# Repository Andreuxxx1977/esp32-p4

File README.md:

KiCad 10 renders of hardware/output/esp32p4_extreme.kicad_pcb (commit ff21bf26fdb5f9f9c406fee58010d21b526a7d88), published by CI.

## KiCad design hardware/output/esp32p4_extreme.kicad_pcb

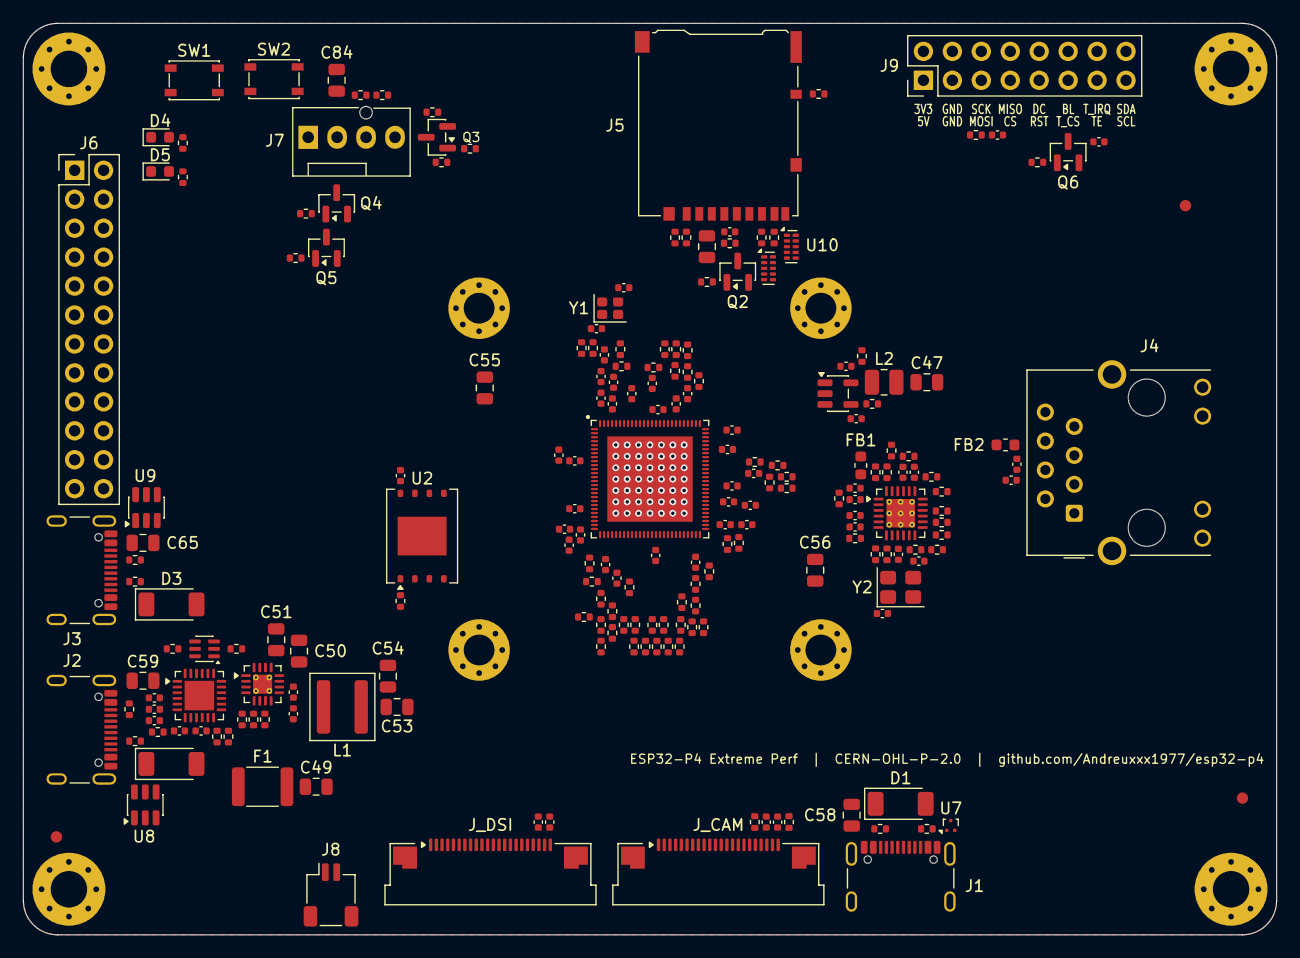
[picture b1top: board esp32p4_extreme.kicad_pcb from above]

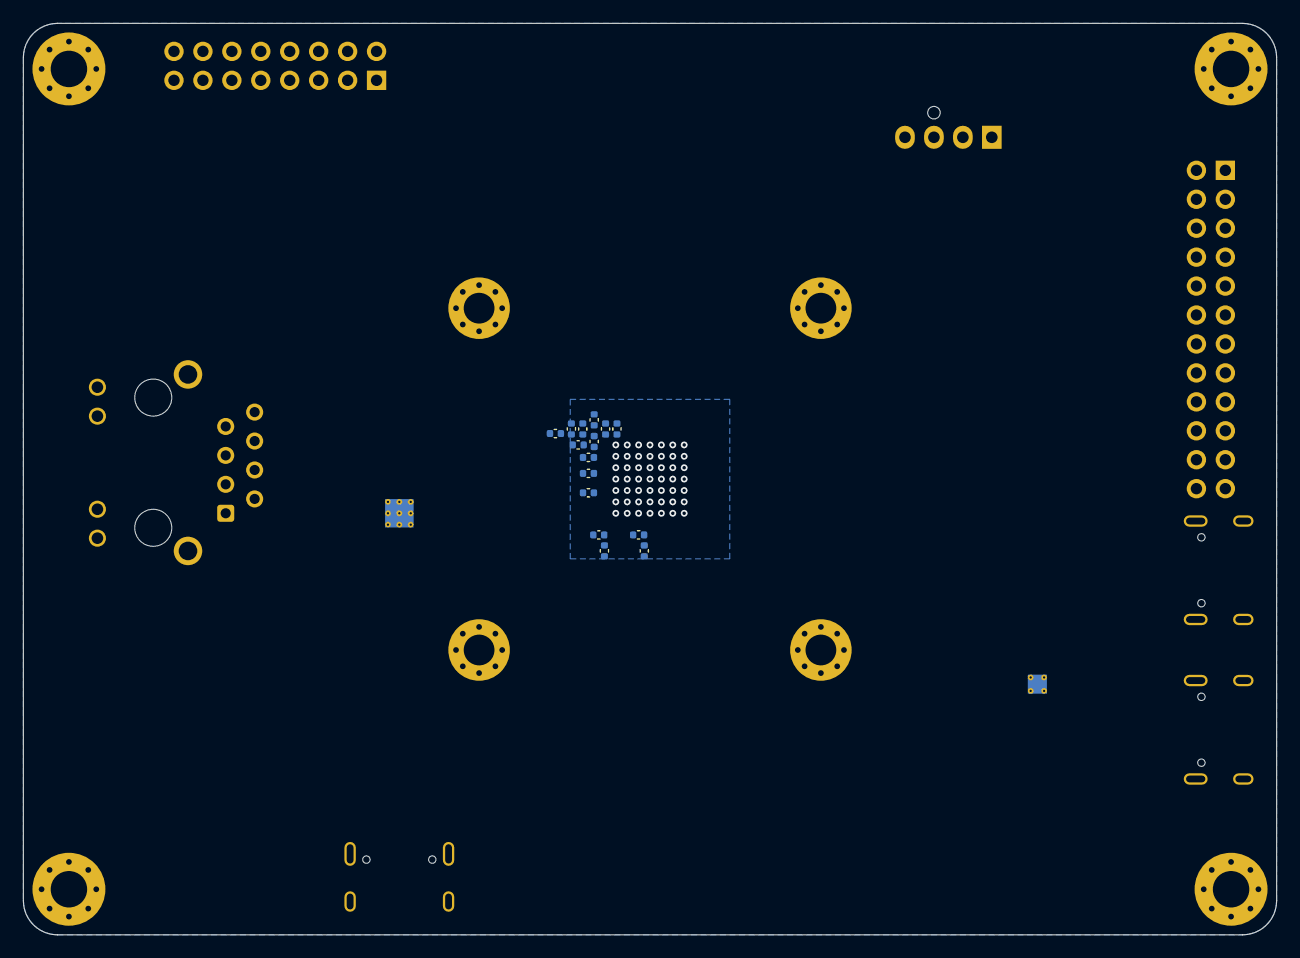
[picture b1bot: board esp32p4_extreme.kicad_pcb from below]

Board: 4 copper layers, 110.0 x 80.0 mm, 234 parts (15 on the bottom side), 175 nets, no tracks yet.

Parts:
C1, C3, C4, C7, C10, C13, C15, C17, C19, C21, C27, C29, C32, C34, C35, C37, C39, C40, C45, C52, C60, C62, C64, C70, C71, C72, C75, C79, C81, C83, C86: 100nF; C_0402_1005Metric
C2, C6, C28, C31, C33, C41: 10uF; C_0402_1005Metric
C5, C8, C11, C16, C18, C20, C22, C23, C24, C25, C26, C30, C36, C42, C61, C63, C68, C69, C73, C80, C82: 1uF; C_0402_1005Metric
C9, C12, C38, C76: 10nF; C_0402_1005Metric
C14, C46: 4.7uF; C_0402_1005Metric
C43, C44: 12pF; C_0402_1005Metric
C47, C53, C54: 22uF; C_0805_2012Metric
C48: 22pF; C_0402_1005Metric
C49, C50, C51, C58, C59, C65, C78, C84: 10uF; C_0805_2012Metric
C55, C56: 47uF; C_0805_2012Metric
C57: 3.3nF; C_0402_1005Metric
C66, C67: 18pF; C_0402_1005Metric
C74: 470pF; C_0402_1005Metric
C77, C85: 10pF; C_0402_1005Metric
D1, D2, D3: PMEG4050EP; D_SOD-128
D4: Green; LED_0603_1608Metric
D5: Red; LED_0603_1608Metric
F1: PTC 2.5A; Fuse_1812_4532Metric
FB1, FB2: 220R@100MHz; L_0603_1608Metric
FID1, FID2, FID3: Fiducial; Fiducial_1mm_Mask2mm
H1, H2, H3, H4: M2.5; MountingHole_2.7mm_M2.5_Pad_Via
H5, H6, H7, H8: M3; MountingHole_3.2mm_M3_Pad_Via
J1, J2, J3: USB-C; USB_C_Receptacle_GCT_USB4105-xx-A_16P_TopMnt_Horizontal
J4: RJ45 MagJack; RJ45_Hanrun_HR911105A_Horizontal
J5: microSD; microSD_HC_Hirose_DM3AT-SF-PEJM5
J6: 2x12 header; PinHeader_2x12_P2.54mm_Vertical
J7: Fan 4P; FanPinHeader_1x04_P2.54mm_Vertical
J8: JST-SH 2P; JST_SH_SM02B-SRSS-TB_1x02-1MP_P1.00mm_Horizontal
J9: 2x8 header; PinHeader_2x08_P2.54mm_Vertical
J_CAM: FPC 22P 0.5mm; Amphenol_F32Q-1A7x1-11022_1x22-1MP_P0.5mm_Horizontal
J_DSI: FPC 22P 0.5mm; Amphenol_F32Q-1A7x1-11022_1x22-1MP_P0.5mm_Horizontal
L1: 2.2uH; L_Coilcraft_XAL5030-XXX
L2: 2.2uH; L_1008_2520Metric
Q1: MMDT3904; SOT-363_SC-70-6
Q2, Q4, Q6: AO3401A; SOT-23
Q3, Q5: AO3400A; SOT-23
R1, R2, R3, R11, R12, R13, R14, R15, R16, R17, R18, R28, R29, R59, R60, R61, R62, R63, R64, R72, R73, R74, R75, R76, R77, R78, R79, R80, R81, R82, R83: 0R; R_0402_1005Metric
R4, R5: 4.02k; R_0402_1005Metric
R6, R7, R8, R19, R35, R36, R49, R50, R51, R70, R71, R88, R90, R91: 10k; R_0402_1005Metric
R9, R25, R34, R92, R93: 1k; R_0402_1005Metric
R10: 1M; R_0402_1005Metric
R20, R21: 499k; R_0402_1005Metric
R22: 75k; R_0402_1005Metric
R23: 24k; R_0402_1005Metric
R24, R87, R89, R95: 100k; R_0402_1005Metric
R26, R27, R30, R31, R37, R38: 5.1k; R_0402_1005Metric
R32: 22.1k; R_0402_1005Metric
R33: 47.5k; R_0402_1005Metric
R39, R40, R41, R42, R43, R44, R45, R46, R94: 22; R_0402_1005Metric
R47: 33; R_0402_1005Metric
R48: 12.1k; R_0402_1005Metric
R52: 1.5k; R_0402_1005Metric
R53, R54, R55, R56: 49.9; R_0402_1005Metric
R57, R58: 330; R_0402_1005Metric
R65, R66, R67, R68, R69: 51k; R_0402_1005Metric
R84, R85: 2.2k; R_0402_1005Metric
R86: 100; R_0402_1005Metric
SW1, SW2: Tactile; SW_SPST_PTS810
U1: ESP32-P4NRW32X; ESP32-P4
U2: W25Q256JV 32MB; WSON-8-1EP_8x6mm_P1.27mm_EP3.4x4.3mm
U3: TPS62130; VQFN-16-1EP_3x3mm_P0.5mm_EP1.68x1.68mm_ThermalVias
U4: TLV62569; SOT-23-5
U5: LAN8720A; VQFN-24-1EP_4x4mm_P0.5mm_EP2.5x2.5mm_ThermalVias
U6: CP2102N; QFN-24-1EP_4x4mm_P0.5mm_EP2.6x2.6mm
U7: TPD2EUSB30; Texas_DRT-3
U8, U9: USBLC6-2SC6; SOT-23-6
U10, U11: TPD4E05U06; USON-10_2.5x1.0mm_P0.5mm
Y1: 40MHz 10ppm; Crystal_SMD_2016-4Pin_2.0x1.6mm
Y2: 25MHz; Crystal_SMD_3225-4Pin_3.2x2.5mm

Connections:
+3V3: C1.1, C2.1, C3.1, C19.1, C20.1, C27.1, C28.1, C32.1, C33.1, C37.1, C38.1, C39.1, C46.1, C53.1, C54.1, C55.1, C56.1, C60.1, C61.1, C62.1, C63.1, C64.1, C72.1, C80.1, C81.1, C82.1, C83.1, FB1.1, J6.1, J9.1, J_CAM.22, J_DSI.22, L1.2, Q2.2, Q6.2, R1.1, R2.1, R6.1, R7.1, R8.1, R22.1, R24.1, R25.1, R34.1, R51.1, R52.1, R71.1, R84.1, R85.1, R90.1, R91.1, U1.9, U1.21, U1.62, U1.75, U1.77, U1.96, U1.101, U3.14, U4.4, U5.9, U6.5, U6.6, U6.7
BOOT_BTN: Q1.3, R9.2, SW2.1
BUCK_FB: R22.2, R23.1, U3.5
BUCK_PG: R24.2, U3.4
BUCK_SS: C57.1, U3.9
BUCK_SW: L1.1, U3.1, U3.2, U3.3
CAM_CLK_N: J_CAM.8, R77.2
CAM_CLK_P: J_CAM.9, R76.2
CAM_D0_N: J_CAM.2, R73.2
CAM_D0_P: J_CAM.3, R72.2
CAM_D1_N: J_CAM.5, R75.2
CAM_D1_P: J_CAM.6, R74.2
CAM_EN: J_CAM.17, U1.13
CAM_IO1: J_CAM.18, U1.14
CHIP_PU: C42.1, Q1.6, R6.2, SW1.1, U1.103
CP_DTR: Q1.4, R35.1, U6.23
CP_RST_N: R34.2, U6.9
CP_RTS: Q1.1, R36.1, U6.19
CP_VBUS_SENSE: R32.2, R33.1, U6.8
CSI_CLK_N: R77.1, U1.45
CSI_CLK_P: R76.1, U1.44
CSI_D0_N: R73.1, U1.42
CSI_D0_P: R72.1, U1.43
CSI_D1_N: R75.1, U1.46
CSI_D1_P: R74.1, U1.47
CSI_REXT: R5.1, U1.48
DISP_CLK_N: J_DSI.8, R83.2
DISP_CLK_P: J_DSI.9, R82.2
DISP_D0_N: J_DSI.2, R79.2
DISP_D0_P: J_DSI.3, R78.2
DISP_D1_N: J_DSI.5, R81.2
DISP_D1_P: J_DSI.6, R80.2
DSI_CLK_N: R83.1, U1.37
DSI_CLK_P: R82.1, U1.38
DSI_D0_N: R79.1, U1.40
DSI_D0_P: R78.1, U1.39
DSI_D1_N: R81.1, U1.36
DSI_D1_P: R80.1, U1.35
DSI_REXT: R4.1, U1.34
ETH_CT: C75.1, C76.1, FB2.2, J4.4, J4.5
ETH_LED_LINK_A: J4.9, R57.2
ETH_LED_SPEED_A: J4.12, R58.2
ETH_MDC: U1.61, U5.13
ETH_MDIO: R52.2, U1.95, U5.12
ETH_PHY_RST_N: R51.2, U1.94, U5.15
ETH_RX_N: J4.6, R56.1, U5.22
ETH_RX_P: J4.3, R55.1, U5.23
ETH_TX_N: J4.2, R54.1, U5.20
ETH_TX_P: J4.1, R53.1, U5.21
FAN_5V: C84.1, J7.2, Q4.3, R88.2
FAN_EN: Q5.1, R90.2, U1.12
FAN_HS_G: Q4.1, Q5.3, R89.2
FAN_PWM: R86.1, U1.10
FAN_PWM_G: Q3.1, R86.2, R87.1
FAN_PWM_OD: J7.4, Q3.3, R88.1
FAN_TACH: R92.2, U1.11
FAN_TACH_RAW: J7.3, R91.2, R92.1
FLASH_CK: R17.1, U1.32
FLASH_CK_M: R17.2, U2.6
FLASH_CS: R13.1, U1.27
FLASH_CS_M: R13.2, R19.2, U2.1
FLASH_D: R18.1, U1.33
FLASH_D_M: R18.2, U2.5
FLASH_HOLD: R16.1, U1.31
FLASH_HOLD_M: R16.2, U2.7
FLASH_Q: R14.1, U1.28
FLASH_Q_M: R14.2, U2.2
FLASH_WP: R15.1, U1.29
FLASH_WP_M: R15.2, U2.3
GND: C1.2, C2.2, C3.2, C4.2, C5.2, C6.2, C7.2, C8.2, C9.2, C10.2, C11.2, C12.2, C13.2, C14.2, C15.2, C16.2, C17.2, C18.2, C19.2, C20.2, C21.2, C22.2, C23.2, C24.2, C25.2, C26.2, C27.2, C28.2, C29.2, C30.2, C31.2, C32.2, C33.2, C34.2, C35.2, C36.2, C37.2, C38.2, C39.2, C40.2, C41.2, C42.2, C43.2, C44.2, C45.2, C46.2, C47.2, C49.2, C50.2, C51.2, C52.2, C53.2, C54.2, C55.2, C56.2, C57.2, C58.2, C59.2, C60.2, C61.2, C62.2, C63.2, C64.2, C65.2, C66.2, C67.2, C68.2, C69.2, C70.2, C71.2, C72.2, C73.2, C74.2, C75.2, C76.2, C77.2, C78.2, C79.2, C80.2, C81.2, C82.2, C83.2, C84.2, C85.2, C86.2, D4.1, D5.1, H1.1, H2.1, H3.1, H4.1, H5.1, H6.1, H7.1, H8.1, J1.A1, J1.A12, J1.B1, J1.B12, J1.SH, J2.A1, J2.A12, J2.B1, J2.B12, J2.SH, J3.A1, J3.A12, J3.B1, J3.B12, J3.SH, J4.8, J4.10, J4.11, J4.SH, J5.6, J5.9, J5.SH, J6.9, J6.10, J7.1, J8.2, J8.MP, J9.3, J9.4, J_CAM.1, J_CAM.4, J_CAM.7, J_CAM.10, J_CAM.13, J_CAM.16, J_CAM.19, J_CAM.MP, J_DSI.1, J_DSI.4, J_DSI.7, J_DSI.10, J_DSI.13, J_DSI.16, J_DSI.19, J_DSI.MP, Q3.2, Q5.2, R4.2, R5.2, R10.2, R21.2, R23.2, R26.2, R27.2, R30.2, R31.2, R33.2, R37.2, R38.2, R48.2, R49.2, R50.2, R70.2, R87.2, R95.2, SW1.2, SW2.2, U1.105, U2.4, U2.9, U3.6, U3.7, U3.8, U3.15, U3.16, U3.17, U4.2, U5.25, U6.2, U6.25, U7.3, U8.2, U9.2, U10.3, U10.8, U11.3, U11.8, Y1.2, Y1.4, Y2.2, Y2.4
GPIO0: J6.3, U1.104
GPIO1: J6.4, U1.1
GPIO2: J6.5, U1.2
GPIO3: J6.6, U1.3
GPIO4: J6.7, U1.4
GPIO5: J6.8, U1.5
GPIO16: J6.15, J9.12, U1.17
GPIO17: J6.16, J9.13, U1.18
GPIO18: J6.17, Q6.1, R95.1, U1.19
GPIO19: J6.18, J9.14, U1.20
GPIO22: J6.19, J9.7, U1.24
GPIO23: J6.20, J9.8, U1.25
GPIO32: J6.21, R94.1, U1.63
GPIO33: J6.22, J9.6, U1.64
GPIO53: J6.23, J9.9, U1.97
GPIO54: J6.24, J9.10, U1.98
HP_SW: L2.1, U4.3
I2C_SCL: J6.12, J9.16, J_CAM.20, J_DSI.20, R85.2, U1.8
I2C_SDA: J6.11, J9.15, J_CAM.21, J_DSI.21, R84.2, U1.7
J1_CC1: J1.A5, R26.1
J1_CC2: J1.B5, R27.1
J2_CC1: J2.A5, R30.1
J2_CC2: J2.B5, R31.1
J3_CC1: J3.A5, R37.1
J3_CC2: J3.B5, R38.1
LCD_BL_PWM: J_DSI.18, U1.55
LCD_RST: J_DSI.17, U1.56
LCD_SPI_BL: C86.1, J9.11, Q6.3
LCD_SPI_SCK: C85.1, J9.5, R94.2
LED_PWR_A: D4.2, R25.2
LED_STATUS: R93.1, U1.6
LED_STATUS_A: D5.2, R93.2
LP_UART_RXD: J6.14, U1.16
LP_UART_TXD: J6.13, U1.15
PHY_AVDD: C68.1, C69.1, C70.1, C71.1, FB1.2, FB2.1, R53.2, R54.2, R55.2, R56.2, U5.1, U5.19
PHY_LED1: R57.1, U5.3
PHY_LED2: R49.1, R58.1, U5.2
PHY_RBIAS: R48.1, U5.24
PHY_RXER: R50.1, U5.10
PHY_VDDCR: C73.1, C74.1, U5.6
PHY_XI: C66.1, U5.5, Y2.1
PHY_XO: C67.1, U5.4, Y2.3
Q1_B1: Q1.2, R35.2
Q1_B2: Q1.5, R36.2
RMII_CRS_DV: R46.2, U1.57
RMII_CRS_DV_PHY: R46.1, U5.11
RMII_REF_CLK: R47.2, U1.93
RMII_REF_CLK_PHY: R47.1, U5.14
RMII_RXD0: R44.2, U1.58
RMII_RXD0_PHY: R44.1, U5.8
RMII_RXD1: R45.2, U1.60
RMII_RXD1_PHY: R45.1, U5.7
RMII_TXD0: R41.1, U1.65
RMII_TXD0_PHY: R41.2, U5.17
RMII_TXD1: R7.2, R9.1, R42.1, U1.66
RMII_TXD1_PHY: R42.2, U5.18
RMII_TX_EN: R43.1, U1.92
RMII_TX_EN_PHY: R43.2, U5.16
SD_CLK: R63.1, U1.84
SD_CLK_C: C77.1, J5.5, R63.2, U11.1, U11.10
SD_CMD: R64.1, U1.86
SD_CMD_C: J5.3, R64.2, R69.1, U11.2, U11.9
SD_D0: R59.1, U1.80
SD_D0_C: J5.7, R59.2, R65.1, U10.1, U10.10
SD_D1: R60.1, U1.81
SD_D1_C: J5.8, R60.2, R66.1, U10.2, U10.9
SD_D2: R61.1, U1.82
SD_D2_C: J5.1, R61.2, R67.1, U10.4, U10.7
SD_D3: R62.1, U1.83
SD_D3_C: J5.2, R62.2, R68.1, U10.5, U10.6
SD_DET: J5.10, R71.2, U1.23, U11.4, U11.7
SD_PWR_EN: Q2.1, R70.1, U1.22
SD_VDD: C78.1, C79.1, J5.4, Q2.3
STRAP_GPIO36: R8.2, U1.68
UART0_RXD: U1.70, U6.21
UART0_TXD: U1.69, U6.20
USB1_D_N: J1.A7, J1.B7, R29.1, U7.2
USB1_D_P: J1.A6, J1.B6, R28.1, U7.1
USB2_D_N: J2.A7, J2.B7, U6.4, U8.3, U8.4
USB2_D_P: J2.A6, J2.B6, U6.3, U8.1, U8.6
USB3_D_N: J3.A7, J3.B7, R40.1, U9.3, U9.4
USB3_D_P: J3.A6, J3.B6, R39.1, U9.1, U9.6
USBHS_D_N: R29.2, U1.49
USBHS_D_P: R10.1, R28.2, U1.50
USJ_D_N: R40.2, U1.52
USJ_D_P: R39.2, U1.53
VBUS1: C58.1, D1.2, J1.A4, J1.A9, J1.B4, J1.B9
VBUS2: C59.1, D2.2, J2.A4, J2.A9, J2.B4, J2.B9, R32.1, U8.5
VBUS3: C65.1, D3.2, J3.A4, J3.A9, J3.B4, J3.B9, U9.5
VDDO_4_SDIO: C26.1, C34.1, R65.2, R66.2, R67.2, R68.2, R69.2, U1.74, U1.85
VDDO_FLASH: C7.1, C8.1, C23.1, C45.1, R19.1, U1.30, U1.71, U2.8
VDDO_PSRAM: C17.1, C18.1, C21.1, C22.1, C24.1, U1.59, U1.67, U1.72
VDD_BAT: C40.1, C41.1, R2.2, U1.102
VDD_HP: C4.1, C5.1, C6.1, C29.1, C30.1, C31.1, C35.1, C36.1, C47.1, C48.1, L2.2, R3.1, R20.1, U1.26, U1.76, U1.91
VDD_HP1_PAD: C15.1, C16.1, R3.2, U1.54
VDD_HP_EN: U1.79, U4.1
VDD_HP_FB: C48.2, R20.2, R21.1, U1.78, U4.5
VDD_MIPI_PHY: C9.1, C10.1, C11.1, C25.1, U1.41, U1.73
VDD_USBPHY: C12.1, C13.1, C14.1, R1.2, U1.51
VSYS_5V: C49.1, C50.1, C51.1, C52.1, F1.2, J6.2, J8.1, J9.2, Q4.2, R89.1, U3.10, U3.11, U3.12, U3.13
VSYS_OR: D1.1, D2.1, D3.1, F1.1
XTAL_N: R12.1, U1.99
XTAL_N_Y: C44.1, R12.2, Y1.3
XTAL_P: R11.1, U1.100
XTAL_P_Y: C43.1, R11.2, Y1.1

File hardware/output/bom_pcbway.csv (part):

Item #,Designator,Quantity,Value/Name,Package/Footprint,Manufacturer Part Number (MPN),Manufacturer,Description,Mount (SMD/THT),LCSC #,Assembly note
1,"C1, C3, C4, C7, C10, C13, C15, C17, C19, C21, C27, C29, C32, C34, C35, C37, C39, C40, C45, C52, C60, C62, C64, C70, C71, C72, C75, C79, C81, C83, C86",31,100nF,0402 [C_0402_1005Metric],CL05B104KO5NNNC,Samsung Electro-Mechanics,MLCC 100nF 16V X7R,SMD,C1525,
2,"C2, C6, C28, C31, C33, C41",6,10uF,0402 [C_0402_1005Metric],CL05A106MQ5NUNC,Samsung Electro-Mechanics,MLCC 10uF 6.3V X5R,SMD,C15525,
3,"C5, C8, C11, C16, C18, C20, C22, C23, C24, C25, C26, C30, C36, C42, C61, C63, C68, C69, C73, C80, C82",21,1uF,0402 [C_0402_1005Metric],CL05A105KA5NQNC,Samsung Electro-Mechanics,MLCC 1uF 25V X5R,SMD,C52923,
4,"C9, C12, C38, C76",4,10nF,0402 [C_0402_1005Metric],CL05B103KB5NNNC,Samsung Electro-Mechanics,MLCC 10nF 50V X7R,SMD,C15195,
5,"C14, C46",2,4.7uF,0402 [C_0402_1005Metric],CL05A475MP5NRNC,Samsung Electro-Mechanics,MLCC 4.7uF 10V X5R,SMD,C23733,
6,"C43, C44",2,12pF,0402 [C_0402_1005Metric],CL05C120JB5NNNC,Samsung Electro-Mechanics,MLCC 12pF 50V C0G,SMD,,no LCSC number
7,"C47, C53, C54",3,22uF,0805 [C_0805_2012Metric],CL21A226MQQNNNE,Samsung Electro-Mechanics,MLCC 22uF 6.3V X5R,SMD,C5674,
8,C48,1,22pF,0402 [C_0402_1005Metric],CL05C220JB5NNNC,Samsung Electro-Mechanics,MLCC 22pF 50V C0G,SMD,C70464,
9,"C49, C50, C51, C58, C59, C65, C78, C84",8,10uF,0805 [C_0805_2012Metric],CL21A106KAYNNNE,Samsung Electro-Mechanics,MLCC 10uF 25V X5R,SMD,C15850,
10,"C55, C56",2,47uF,0805 [C_0805_2012Metric],CL21A476MQYNNNE,Samsung Electro-Mechanics,MLCC 47uF 6.3V X5R,SMD,C16780,
11,C57,1,3.3nF,0402 [C_0402_1005Metric],CL05B332KB5NNNC,Samsung Electro-Mechanics,MLCC 3.3nF 50V X7R,SMD,C26404,
12,"C66, C67",2,18pF,0402 [C_0402_1005Metric],CL05C180JB5NNNC,Samsung Electro-Mechanics,MLCC 18pF 50V C0G,SMD,C307443,
13,C74,1,470pF,0402 [C_0402_1005Metric],CL05B471KB5NNNC,Samsung Electro-Mechanics,MLCC 470pF 50V X7R,SMD,C26412,
14,"D1, D2, D3",3,PMEG4050EP,SOD-128 [D_SOD-128],"PMEG4050EP,115",Nexperia,40 V 5 A low-VF Schottky (~0.4 V @ 2.5 A) -- VBUS OR-ing,SMD,C96235,
15,D4,1,Green,0603 [LED_0603_1608Metric],150060GS75000,Wurth Elektronik,Green LED,SMD,C5252984,
16,D5,1,Red,0603 [LED_0603_1608Metric],150060RS75000,Wurth Elektronik,Red LED,SMD,C3030991,
17,F1,1,PTC 2.5A,1812 [Fuse_1812_4532Metric],MF-MSMF250/16X-2,Bourns,"Resettable fuse, 2.5 A hold / 5 A trip, 16 V, on VSYS",SMD,C210838,
18,"FB1, FB2",2,220R@100MHz,0603 [L_0603_1608Metric],BLM18PG221SN1D,Murata,"Ferrite bead 220 ohm, 1.4 A",SMD,C80165,
19,"J1, J2, J3",3,USB-C,"USB Type-C 16P, top-mount [USB_C_Receptacle_GCT_USB4105-xx-A_16P_TopMnt_Horizontal]",USB4105-GF-A,GCT,"USB 2.0 Type-C receptacle (UFP, 5.1k Rd); SMD contacts + 4 THT shell legs",SMD,C3020560,SMD with THT legs (paste-in-hole / hand-solder the legs)
20,J4,1,RJ45 MagJack,"RJ45 THT, integrated magnetics + 2 LEDs [RJ45_Hanrun_HR911105A_Horizontal]",HR911105A,HanRun,"RJ45 with 10/100 magnetics (1:1, CT) and green/yellow LEDs",THT,C12074,"THT, top side"
21,J5,1,microSD,"microSD push-push, SMT [microSD_HC_Hirose_DM3AT-SF-PEJM5]",DM3AT-SF-PEJM5,Hirose,microSD socket with card-detect switch,SMD,C114218,
22,J6,1,2x12 header,2x12 2.54 mm THT [PinHeader_2x12_P2.54mm_Vertical],61302421121,Wurth Elektronik,2x12 expansion header,THT,,"THT, top side; no LCSC number"
23,J7,1,Fan 4P,"2.54 mm 4-pin fan header, THT [FanPinHeader_1x04_P2.54mm_Vertical]",47053-1000,Molex,"Intel 4-wire PWM fan header (1 GND, 2 +V, 3 TACH, 4 PWM)",THT,C240840,"THT, top side"
24,J8,1,JST-SH 2P,"JST SH 1.0 mm 2P, SMT [JST_SH_SM02B-SRSS-TB_1x02-1MP_P1.00mm_Horizontal]",SM02B-SRSS-TB(LF)(SN),JST,Display backlight 5 V feed,SMD,C160402,
25,J9,1,2x8 header,2x8 2.54 mm THT [PinHeader_2x08_P2.54mm_Vertical],61301621121,Wurth Elektronik,2x8 SPI/I2C TFT display header (dupont-wire friendly),THT,,"THT, top side; no LCSC number"
26,"J_CAM, J_DSI",2,FPC 22P 0.5mm,"FPC 22P 0.5 mm, top contact, horizontal, SMT [Amphenol_F32Q-1A7x1-11022_1x22-1MP_P0.5mm_Horizontal]",F32Q-1A7H1-11022,Amphenol ICC,"22-pin 0.5 mm FPC, same top-contact part as Raspberry Pi 5 -> standard Pi cables, no mirroring",SMD,C3169253,
27,L1,1,2.2uH,5.3x5.5 mm shielded [L_Coilcraft_XAL5030-XXX],XAL5030-222MEC,Coilcraft,"2.2 uH, Isat 9.2 A, DCR 14.5 mOhm -- 3 A buck inductor",SMD,C920280,
28,L2,1,2.2uH,2520 (1008) metal alloy [L_1008_2520Metric],DFE252012F-2R2M=P2,Murata,"2.2 uH, Isat 3.3 A, 82 mOhm -- VDD_HP buck inductor",SMD,C576403,
29,Q1,1,MMDT3904,SOT-363 [SOT-363_SC-70-6],MMDT3904-7-F,Diodes Incorporated,Dual NPN for DTR/RTS auto-reset + boot-strap circuit,SMD,C83572,
30,"Q2, Q4, Q6",3,AO3401A,SOT-23 [SOT-23],AO3401A,Alpha & Omega Semiconductor,-30 V -4 A P-MOSFET (high-side load switch),SMD,C15127,
31,"Q3, Q5",2,AO3400A,SOT-23 [SOT-23],AO3400A,Alpha & Omega Semiconductor,30 V 5.7 A logic-level N-MOSFET (Vgs(th) 1.45 V max),SMD,C20917,
32,"R1, R2, R3, R11, R12, R13, R14, R15, R16, R17, R18, R28, R29, R59, R60, R61, R62, R63, R64, R72, R73, R74, R75, R76, R77, R78, R79, R80, R81, R82, R83",31,0R,0402 [R_0402_1005Metric],RC0402JR-070RL,YAGEO,"Thick-film resistor, jumper",SMD,C60485,
33,"R4, R5",2,4.02k,0402 [R_0402_1005Metric],RC0402FR-074K02L,YAGEO,"Thick-film resistor, 1 %, 1/16 W",SMD,,no LCSC number
34,"R6, R7, R8, R19, R35, R36, R49, R50, R51, R70, R71, R90, R91",13,10k,0402 [R_0402_1005Metric],RC0402FR-0710KL,YAGEO,"Thick-film resistor, 1 %, 1/16 W",SMD,C60490,
35,"R9, R25, R34, R92, R93",5,1k,0402 [R_0402_1005Metric],RC0402FR-071KL,YAGEO,"Thick-film resistor, 1 %, 1/16 W",SMD,C106235,
36,"R20, R21",2,499k,0402 [R_0402_1005Metric],RC0402FR-07499KL,YAGEO,"Thick-film resistor, 1 %, 1/16 W",SMD,,no LCSC number
37,R22,1,75k,0402 [R_0402_1005Metric],RC0402FR-0775KL,YAGEO,"Thick-film resistor, 1 %, 1/16 W",SMD,,no LCSC number
38,R23,1,24k,0402 [R_0402_1005Metric],RC0402FR-0724KL,YAGEO,"Thick-film resistor, 1 %, 1/16 W",SMD,,no LCSC number
39,"R24, R87, R89, R95",4,100k,0402 [R_0402_1005Metric],RC0402FR-07100KL,YAGEO,"Thick-film resistor, 1 %, 1/16 W",SMD,,no LCSC number
40,"R26, R27, R30, R31, R37, R38",6,5.1k,0402 [R_0402_1005Metric],RC0402FR-075K1L,YAGEO,"Thick-film resistor, 1 %, 1/16 W",SMD,,no LCSC number
41,R32,1,22.1k,0402 [R_0402_1005Metric],RC0402FR-0722K1L,YAGEO,"Thick-film resistor, 1 %, 1/16 W",SMD,,no LCSC number
42,R33,1,47.5k,0402 [R_0402_1005Metric],RC0402FR-0747K5L,YAGEO,"Thick-film resistor, 1 %, 1/16 W",SMD,,no LCSC number
43,"R39, R40, R41, R42, R43, R44, R45, R46, R94",9,22,0402 [R_0402_1005Metric],RC0402FR-0722RL,YAGEO,"Thick-film resistor, 1 %, 1/16 W",SMD,,no LCSC number
44,R47,1,33,0402 [R_0402_1005Metric],RC0402FR-0733RL,YAGEO,"Thick-film resistor, 1 %, 1/16 W",SMD,,no LCSC number
45,R48,1,12.1k,0402 [R_0402_1005Metric],RC0402FR-0712K1L,YAGEO,"Thick-film resistor, 1 %, 1/16 W",SMD,,no LCSC number
46,R52,1,1.5k,0402 [R_0402_1005Metric],RC0402FR-071K5L,YAGEO,"Thick-film resistor, 1 %, 1/16 W",SMD,,no LCSC number
47,"R53, R54, R55, R56",4,49.9,0402 [R_0402_1005Metric],RC0402FR-0749R9L,YAGEO,"Thick-film resistor, 1 %, 1/16 W",SMD,C87044,
48,"R57, R58",2,330,0402 [R_0402_1005Metric],RC0402FR-07330RL,YAGEO,"Thick-film resistor, 1 %, 1/16 W",SMD,,no LCSC number
49,"R65, R66, R67, R68, R69",5,51k,0402 [R_0402_1005Metric],RC0402FR-0751KL,YAGEO,"Thick-film resistor, 1 %, 1/16 W",SMD,,no LCSC number
50,"R84, R85",2,2.2k,0402 [R_0402_1005Metric],RC0402FR-072K2L,YAGEO,"Thick-film resistor, 1 %, 1/16 W",SMD,,no LCSC number
51,R86,1,100,0402 [R_0402_1005Metric],RC0402FR-07100RL,YAGEO,"Thick-film resistor, 1 %, 1/16 W",SMD,,no LCSC number
52,"SW1, SW2",2,Tactile,4.2x3.2 mm SMD [SW_SPST_PTS810],PTS810SJM250SMTRLFS,C&K,SMD tactile switch,SMD,C116501,
53,U1,1,ESP32-P4NRW32X,"QFN-104 10x10 mm, 0.35 mm pitch, EPAD 7.5 mm [ESP32-P4]",ESP32-P4NRW32X,Espressif Systems,"Dual-core RISC-V 400 MHz SoC, 32 MB in-package PSRAM, chip rev v3.x",SMD,C54540373,EPAD on the capped via-in-pad array; fine pitch 0.35 mm
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
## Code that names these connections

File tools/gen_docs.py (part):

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          f"{ranges(sd_pads)}) or the NC VDD_IO_5 pads:", "",
          md_table(["Signal", "All legal", "SDIO-free", "Chosen", "Consequence"], forced), "",
          "TXD0/TXD1 have no SDIO-free option except the strapping pins GPIO34/GPIO35, which is why "
          "GPIO35 carries both RMII_TXD1 and the BOOT strap (see section 4).", ""]
    return L


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    L += [md_table([f"GPIO{b}", f"GPIO{q}", "Boot mode", "How the board gets there"], [
        ["1", "x", "SPI boot (normal)", f"{pull_b} pull-up holds GPIO{b} high"],
        ["0", "1", "Joint download boot (UART0 / USB)",
         f"{' or '.join(lows) or '?'} pulls GPIO{b} low while CHIP_PU rises; {pull_q} keeps GPIO{q} = 1"],
        ["0", "0", "not a listed boot mode", f"prevented: nothing in the netlist pulls GPIO{q} low"],
    ], "ccll"), ""]
    pad = p4.GPIO_PAD[b]
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        rows.append(["RMII 50 MHz clock", "series resistor at the clock driver",
                     ", ".join(f"{c.ref} {c.value} ohm ({esc(c.note)})" for c in ser) or "none",
                     status(bool(ser))])
    rmii = [u for u in bs.GPIO_MAP if u.net.startswith("RMII_") and u.net != "RMII_REF_CLK"]
    ser = []
    for u in rmii:
        for c, pad in members(u.net):
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        L += ["```text", *problems, "```", ""]
    L += _architecture()
    used = len(USE)
    L += ["## 2. Pinout", "", "### 2.1 GPIO0-GPIO54", "",
          f"{used} GPIOs used, {len(bs.GPIO_NC)} NC, {55 - used - len(bs.GPIO_NC)} undecided. "
          "Mux: *IO_MUX fixed* = the peripheral only works on this pad; *GPIO matrix* = routed through "
          "the GPIO matrix (any pad); *GPIO* = plain software GPIO; *Strap* = strap-only. "
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         "fan GPIOs floating, so the fan is powered and at 100 %. Firmware only ever *reduces* cooling.", "",
         f"### 7.1 Suggested firmware fan curve (P4 internal temperature sensor, {f(FAN_HYST_K, 0)} K hysteresis)", "",
         md_table(["Die temperature", "Fan duty", f"LEDC duty on GPIO{g_pwm} (inverted by {q_pwm.ref if q_pwm else '?'})",
                   f"GPIO{g_en} FAN_EN"], curve), "",
         "Starting values only -- retune once the thermal numbers in section 3 are measured. Update once per "
         "second, slew-limit the duty (~5 %/s) to avoid audible hunting, and treat a tach reading below "
         "~300 RPM for 3 s while duty >= 30 % as a stalled fan (force 100 %, flag an error).", "",
         "```c",
         "// ESP-IDF sketch -- GPIO numbers generated from board_spec.GPIO_MAP",
         f"#define FAN_PWM_GPIO  {g_pwm}   // LEDC, 25 kHz; output inverted by the open-drain FET",
         f"#define FAN_TACH_GPIO {g_tach}  // PCNT, falling edges, glitch filter ~1 us",
         f"#define FAN_EN_GPIO   {g_en}  // high = fan powered (board default via pull-up)",
         "temperature_sensor_handle_t ts;               // driver/temperature_sensor.h",
         "temperature_sensor_config_t tcfg = TEMPERATURE_SENSOR_CONFIG_DEFAULT(20, 100);",
         "temperature_sensor_install(&tcfg, &ts); temperature_sensor_enable(ts);",
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         "    float t; int duty = 100;                  // fail-safe default",
         "    if (temperature_sensor_get_celsius(ts, &t) == ESP_OK) duty = fan_curve(t);  // table above",
         "    if (tach_stalled(duty)) duty = 100;",
         "    gpio_set_level(FAN_EN_GPIO, duty > 0);",
         "    ledc_set_duty(LEDC_LOW_SPEED_MODE, LEDC_CHANNEL_0, ((100 - duty) * LEDC_MAX) / 100);",
         "    ledc_update_duty(LEDC_LOW_SPEED_MODE, LEDC_CHANNEL_0);",
         "    vTaskDelay(pdMS_TO_TICKS(1000));",
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

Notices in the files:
hardware/output/esp32p4_extreme.kicad_pcb:
github.com/Andreuxxx1977/esp32-p4 -- CERN-OHL-P-2.0
ESP32-P4 Extreme Perf  |  CERN-OHL-P-2.0  |  github.com/Andreuxxx1977/esp32-p4
